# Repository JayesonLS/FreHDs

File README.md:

FreHDs
======

OriginalVecovenFiles
--------------------

An unmodified copy of Frederic Vecoven's 2.14 file release for
easy reference.

OriginalFreHDKiCad
------------------

Frederic Vecoven's original schematic transcribed into KiCard to 
use as a starting point for derivative projects. 

[Latest schematic PDF](OriginalFreHDKiCad/OriginalFreHDKiCad.pdf)

A PCB layout has also been created using the original gerbers. 
Note however that this was used for checking the correctness of the
schematic and is not intended for production. Some of the footprints
and clearances are very rough and should be corrected / cleaned up
before attempting to produce boards. Just use the original gerbers instead.

_Derivative projects may follow, time permitting._

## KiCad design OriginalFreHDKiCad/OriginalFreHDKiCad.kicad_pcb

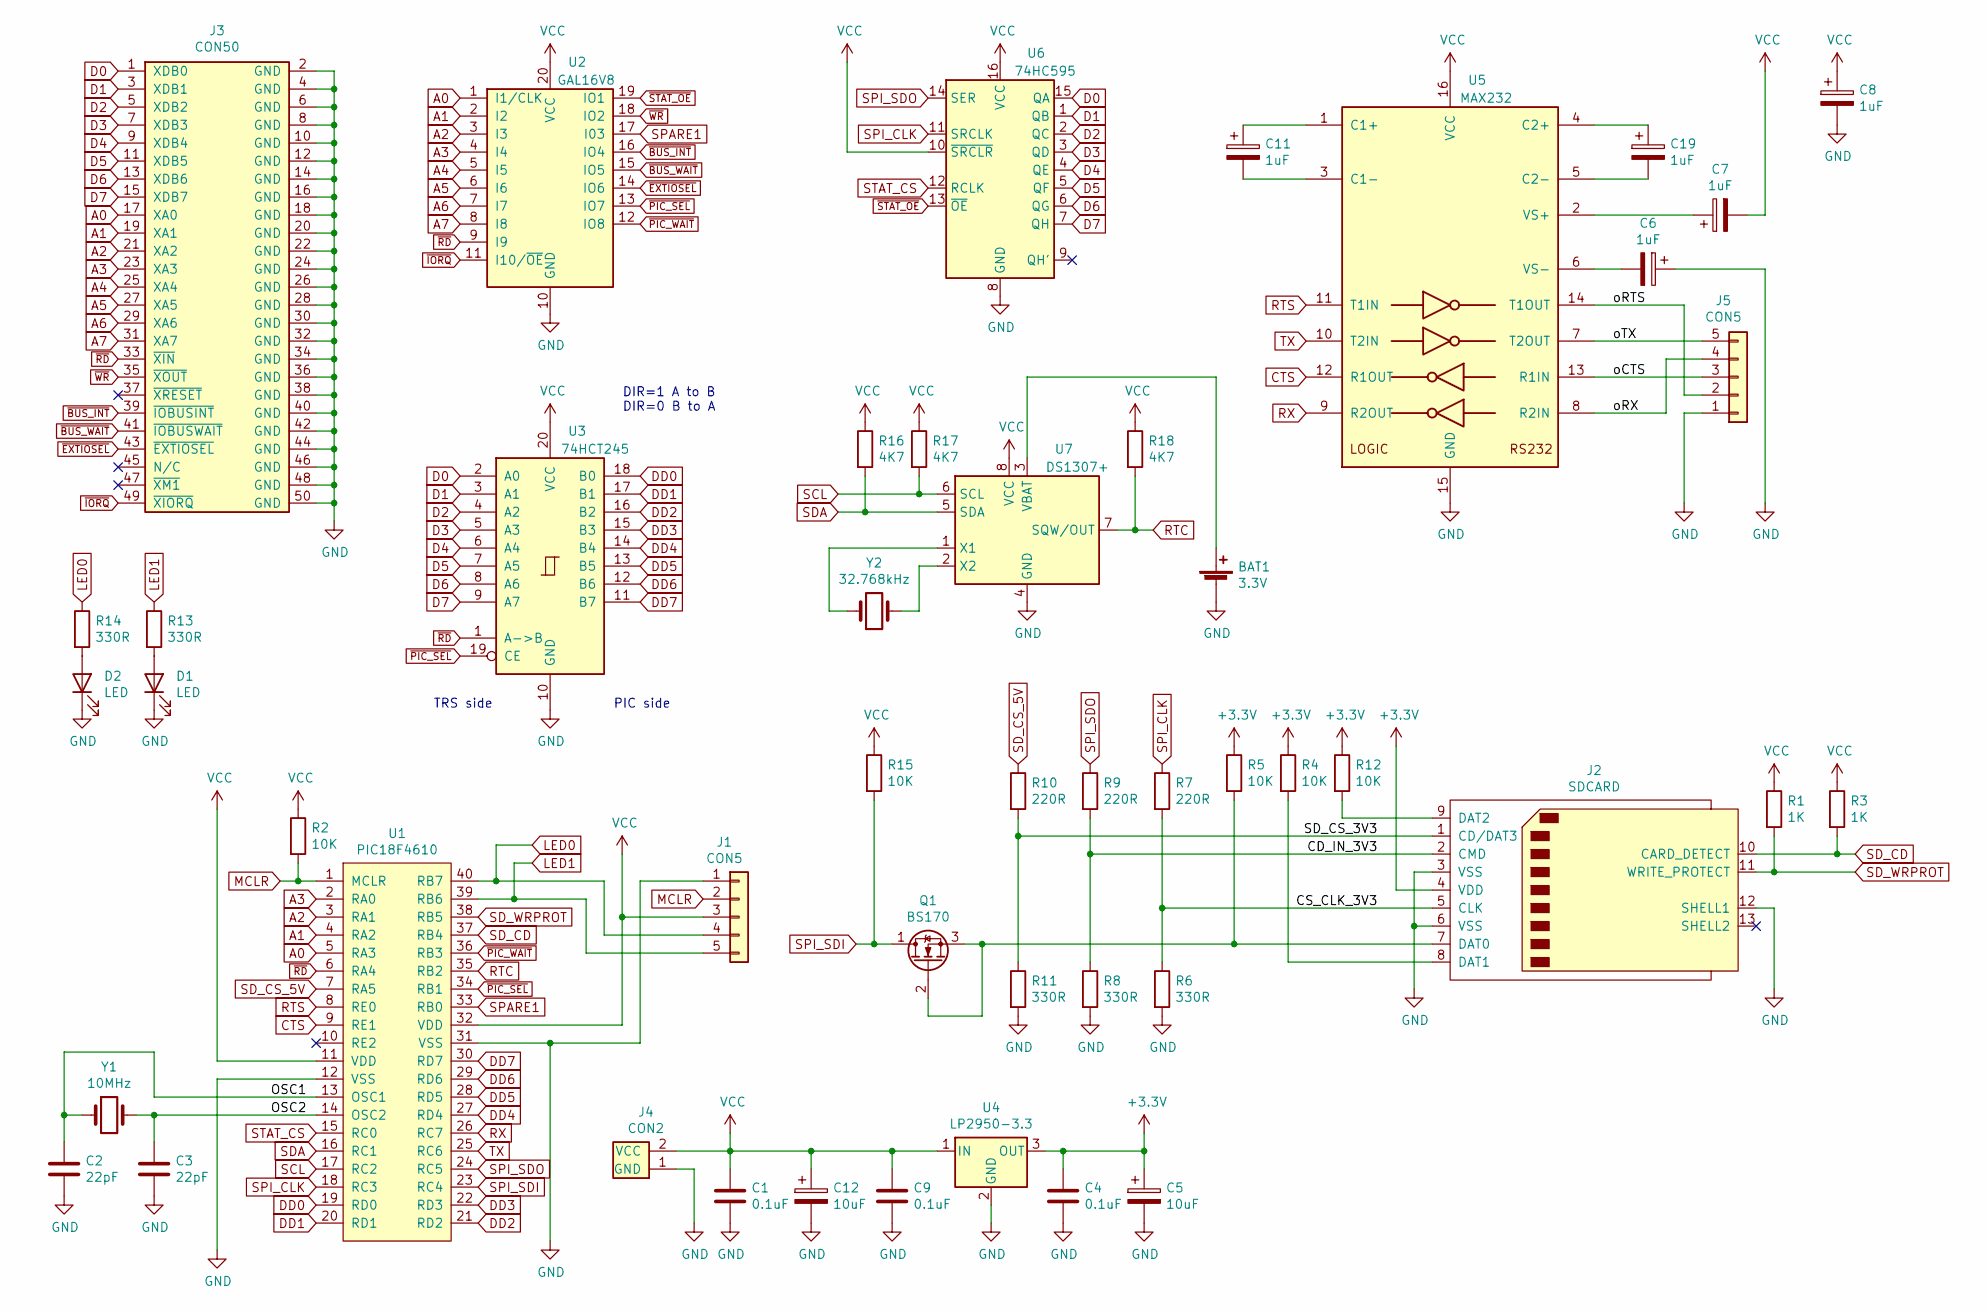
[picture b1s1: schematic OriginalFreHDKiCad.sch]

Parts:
BAT1: 3.3V; BatteryHolder_Keystone_1060_1x2032
C1, C4, C9: 0.1uF; C_Disc_D8.0mm_W2.5mm_P5.00mm
C2, C3: 22pF; C_Disc_D8.0mm_W2.5mm_P5.00mm
C5, C12: 10uF; CP_Radial_D7.5mm_P2.50mm
C6, C7, C8, C11, C19: 1uF; CP_Radial_D7.5mm_P2.50mm
D1, D2: LED; LED_D5.0mm
J1, J5: CON5; PinHeader_1x05_P2.54mm_Vertical
J2: SDCARD; SD_TE_2041021
J3: CON50; PinHeader_2x25_P2.54mm_Vertical
J4: CON2; PinHeader_2x01_P2.54mm_Vertical
Q1: BS170; TO-92
R1, R3: 1K; R_Axial_DIN0207_L6.3mm_D2.5mm_P10.16mm_Horizontal
R2, R4, R5, R12, R15: 10K; R_Axial_DIN0207_L6.3mm_D2.5mm_P10.16mm_Horizontal
R6, R8, R11, R13, R14: 330R; R_Axial_DIN0207_L6.3mm_D2.5mm_P10.16mm_Horizontal
R7, R9, R10: 220R; R_Axial_DIN0207_L6.3mm_D2.5mm_P10.16mm_Horizontal
R16, R17, R18: 4K7; R_Axial_DIN0207_L6.3mm_D2.5mm_P10.16mm_Horizontal
U1: PIC18F4610; DIP-40_W15.24mm
U2: GAL16V8; DIP-20_W7.62mm
U3: 74HCT245; DIP-20_W7.62mm
U4: LP2950-3.3; TO-92
U5: MAX232; DIP-16_W7.62mm
U6: 74HC595; DIP-16_W7.62mm
U7: DS1307+; DIP-8_W7.62mm
Y1: 10MHz; Crystal_HC50_Vertical
Y2: 32.768kHz; Crystal_C38-LF_D3.0mm_L8.0mm_Horizontal

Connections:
+3V3: C4.1, C5.1, J2.4 (VDD), R4.1, R5.1, R12.1, U4.3 (OUT)
/CD_IN_3V3: J2.2 (CMD), R8.1, R9.2
/CS_CLK_3V3: J2.5 (CLK), R6.1, R7.2
/OSC1: C2.1, U1.13 (OSC1), Y1.1
/OSC2: C3.1, U1.14 (OSC2), Y1.2
/SD_CS_3V3: J2.1 (CD/DAT3), R10.2, R11.1
/oCTS: J5.3, U5.13 (R1IN)
/oRTS: J5.2, U5.14 (T1OUT)
/oRX: J5.4, U5.8 (R2IN)
/oTX: J5.5, U5.7 (T2OUT)
A0: J3.17 (XA0), U1.5 (RA3), U2.1 (I1/CLK)
A1: J3.19 (XA1), U1.4 (RA2), U2.2 (I2)
A2: J3.21 (XA2), U1.3 (RA1), U2.3 (I3)
A3: J3.23 (XA3), U1.2 (RA0), U2.4 (I4)
A4: J3.25 (XA4), U2.5 (I5)
A5: J3.27 (XA5), U2.6 (I6)
A6: J3.29 (XA6), U2.7 (I7)
A7: J3.31 (XA7), U2.8 (I8)
CTS: U1.9 (RE1), U5.12 (R1OUT)
D0: J3.1 (XDB0), U3.2 (A0), U6.15 (QA)
D1: J3.3 (XDB1), U3.3 (A1), U6.1 (QB)
D2: J3.5 (XDB2), U3.4 (A2), U6.2 (QC)
D3: J3.7 (XDB3), U3.5 (A3), U6.3 (QD)
D4: J3.9 (XDB4), U3.6 (A4), U6.4 (QE)
D5: J3.11 (XDB5), U3.7 (A5), U6.5 (QF)
D6: J3.13 (XDB6), U3.8 (A6), U6.6 (QG)
D7: J3.15 (XDB7), U3.9 (A7), U6.7 (QH)
DD0: U1.19 (RD0), U3.18 (B0)
DD1: U1.20 (RD1), U3.17 (B1)
DD2: U1.21 (RD2), U3.16 (B2)
DD3: U1.22 (RD3), U3.15 (B3)
DD4: U1.27 (RD4), U3.14 (B4)
DD5: U1.28 (RD5), U3.13 (B5)
DD6: U1.29 (RD6), U3.12 (B6)
DD7: U1.30 (RD7), U3.11 (B7)
GND: BAT1.2 (-), C1.2, C2.2, C3.2, C4.2, C5.2, C6.1, C8.2, C9.2, C12.2, D1.1 (K), D2.1 (K), J1.1, J2.3 (VSS), J2.6 (VSS), J2.12 (SHELL1), J3.2 (GND), J3.4 (GND), J3.6 (GND), J3.8 (GND), J3.10 (GND), J3.12 (GND), J3.14 (GND), J3.16 (GND), J3.18 (GND), J3.20 (GND), J3.22 (GND), J3.24 (GND), J3.26 (GND), J3.28 (GND), J3.30 (GND), J3.32 (GND), J3.34 (GND), J3.36 (GND), J3.38 (GND), J3.40 (GND), J3.42 (GND), J3.44 (GND), J3.46 (GND), J3.48 (GND), J3.50 (GND), J4.1 (GND), J5.1, R6.2, R8.2, R11.2, U1.12 (VSS), U1.31 (VSS), U2.10 (GND), U3.10 (GND), U4.2 (GND), U5.15 (GND), U6.8 (GND), U7.4 (GND)
LED0: J1.4, R14.1, U1.40 (RB7)
LED1: J1.5, R13.1, U1.39 (RB6)
MCLR: J1.2, R2.2, U1.1 (MCLR)
unnamed: BAT1.1 (+), U7.3 (VBAT)
unnamed: C6.2, U5.6 (VS-)
unnamed: C7.1, U5.2 (VS+)
unnamed: C11.1, U5.1 (C1+)
unnamed: C11.2, U5.3 (C1-)
unnamed: C19.1, U5.4 (C2+)
unnamed: C19.2, U5.5 (C2-)
unnamed: D1.2 (A), R13.2
unnamed: D2.2 (A), R14.2
unnamed: J2.7 (DAT0), Q1.2 (G), Q1.3 (S), R5.2
unnamed: J2.8 (DAT1), R4.2
unnamed: J2.9 (DAT2), R12.2
unnamed: U7.1 (X1), Y2.1
unnamed: U7.2 (X2), Y2.2
RTC: R18.2, U1.35 (RB2), U7.7 (SQW/OUT)
RTS: U1.8 (RE0), U5.11 (T1IN)
RX: U1.26 (RC7), U5.9 (R2OUT)
SCL: R17.2, U1.17 (RC2), U7.6 (SCL)
SDA: R16.2, U1.16 (RC1), U7.5 (SDA)
SD_CD: J2.10 (CARD_DETECT), R3.2, U1.37 (RB4)
SD_CS_5V: R10.1, U1.7 (RA5)
SD_WRPROT: J2.11 (WRITE_PROTECT), R1.2, U1.38 (RB5)
SPARE1: U1.33 (RB0), U2.17 (I03)
SPI_CLK: R7.1, U1.18 (RC3), U6.11 (SRCLK)
SPI_SDI: Q1.1 (D), R15.2, U1.23 (RC4)
SPI_SDO: R9.1, U1.24 (RC5), U6.14 (SER)
STAT_CS: U1.15 (RC0), U6.12 (RCLK)
TX: U1.25 (RC6), U5.10 (T2IN)
VCC: C1.1, C7.2, C8.1, C9.1, C12.1, J1.3, J4.2 (VCC), R1.1, R2.1, R3.1, R15.1, R16.1, R17.1, R18.1, U1.11 (VDD), U1.32 (VDD), U2.20 (VCC), U3.20 (VCC), U4.1 (IN), U5.16 (VCC), U6.10 (~SRCLR), U6.16 (VCC), U7.8 (VCC)
~BUS_INT: J3.39 (~IOBUSINT), U2.16 (IO4)
~BUS_WAIT: J3.41 (~IOBUSWAIT), U2.15 (IO5)
~EXTIOSEL: J3.43 (~EXTIOSEL), U2.14 (IO6)
~IORQ: J3.49 (~XIORQ), U2.11 (I10/~OE~)
~PIC_SEL: U1.34 (RB1), U2.13 (IO7), U3.19 (CE)
~PIC_WAIT: U1.36 (RB3), U2.12 (IO8)
~RD: J3.33 (~XIN), U1.6 (RA4), U2.9 (I9), U3.1 (A->B)
~STAT_OE: U2.19 (IO1), U6.13 (~OE)
~WR: J3.35 (~XOUT), U2.18 (IO2)

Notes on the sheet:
TRS side
PIC side
DIR=1 A to B DIR=0 B to A

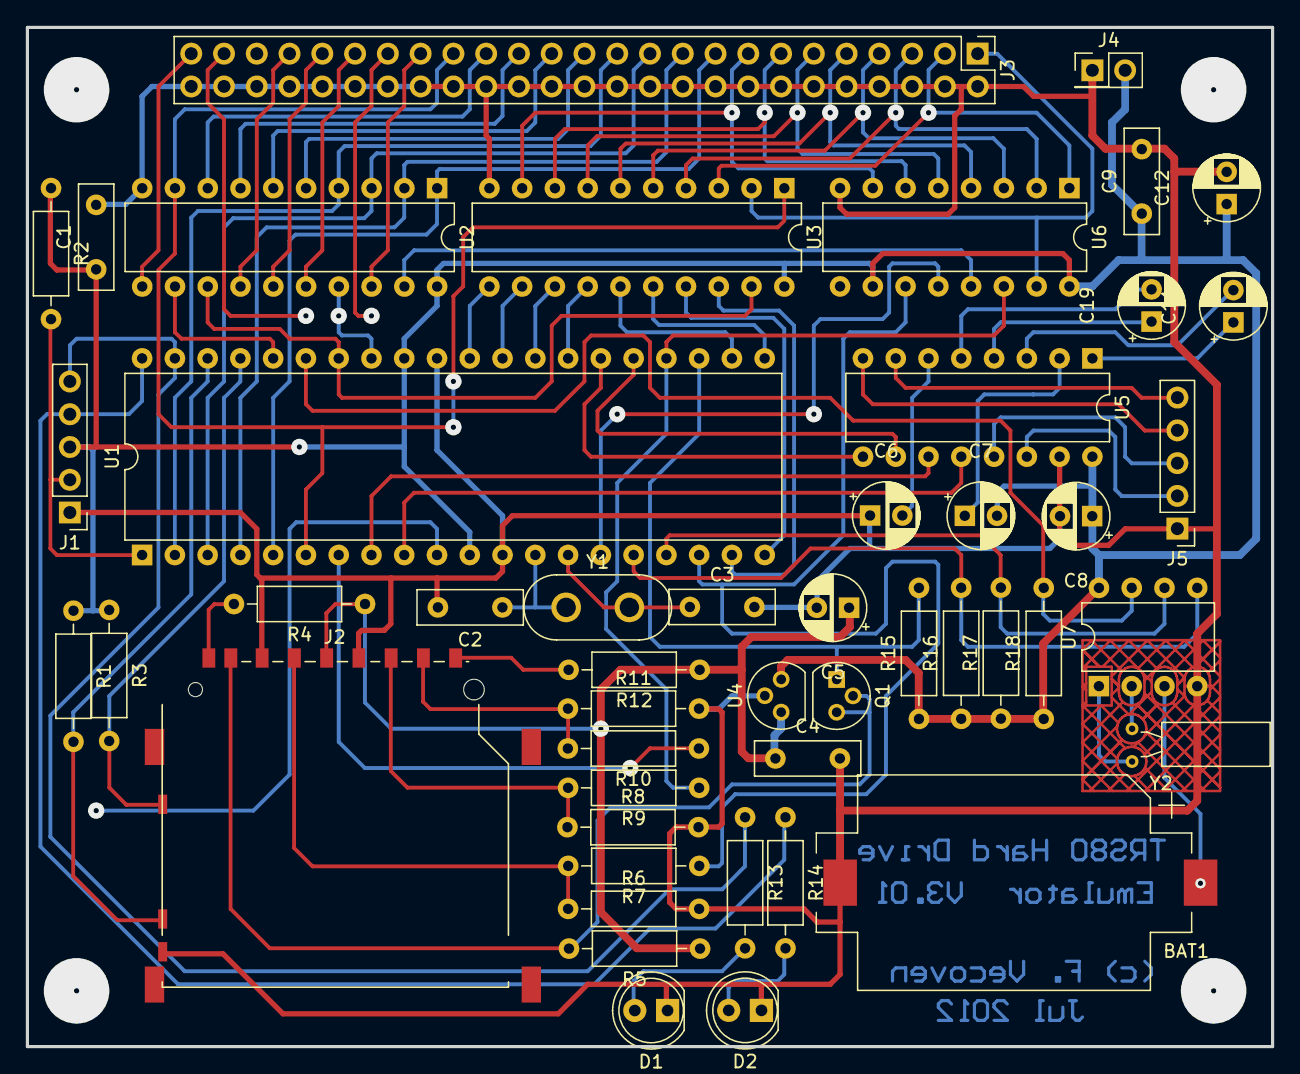
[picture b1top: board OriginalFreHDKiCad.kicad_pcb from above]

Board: 2 copper layers, 96.5 x 79.0 mm, 48 parts (0 on the bottom side), 77 nets.

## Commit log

2021-04-11 Add original FreHD source files from Frederic Vecoven's web site.
2021-04-11 Additional readme for original FreHD files.
2021-04-11 Add license file.
2021-04-11 Initial pass at entering orignal FreHD schematic into KiCad.
2021-04-11 Initial import of original gerbers into pcbnew.
2021-04-11 WIP on matching scheamtic to imported gerbers.
2021-04-12 Finish matching schematic to imported gerbers - the process found one small error.
2021-04-12 Add PDF of schematic.
